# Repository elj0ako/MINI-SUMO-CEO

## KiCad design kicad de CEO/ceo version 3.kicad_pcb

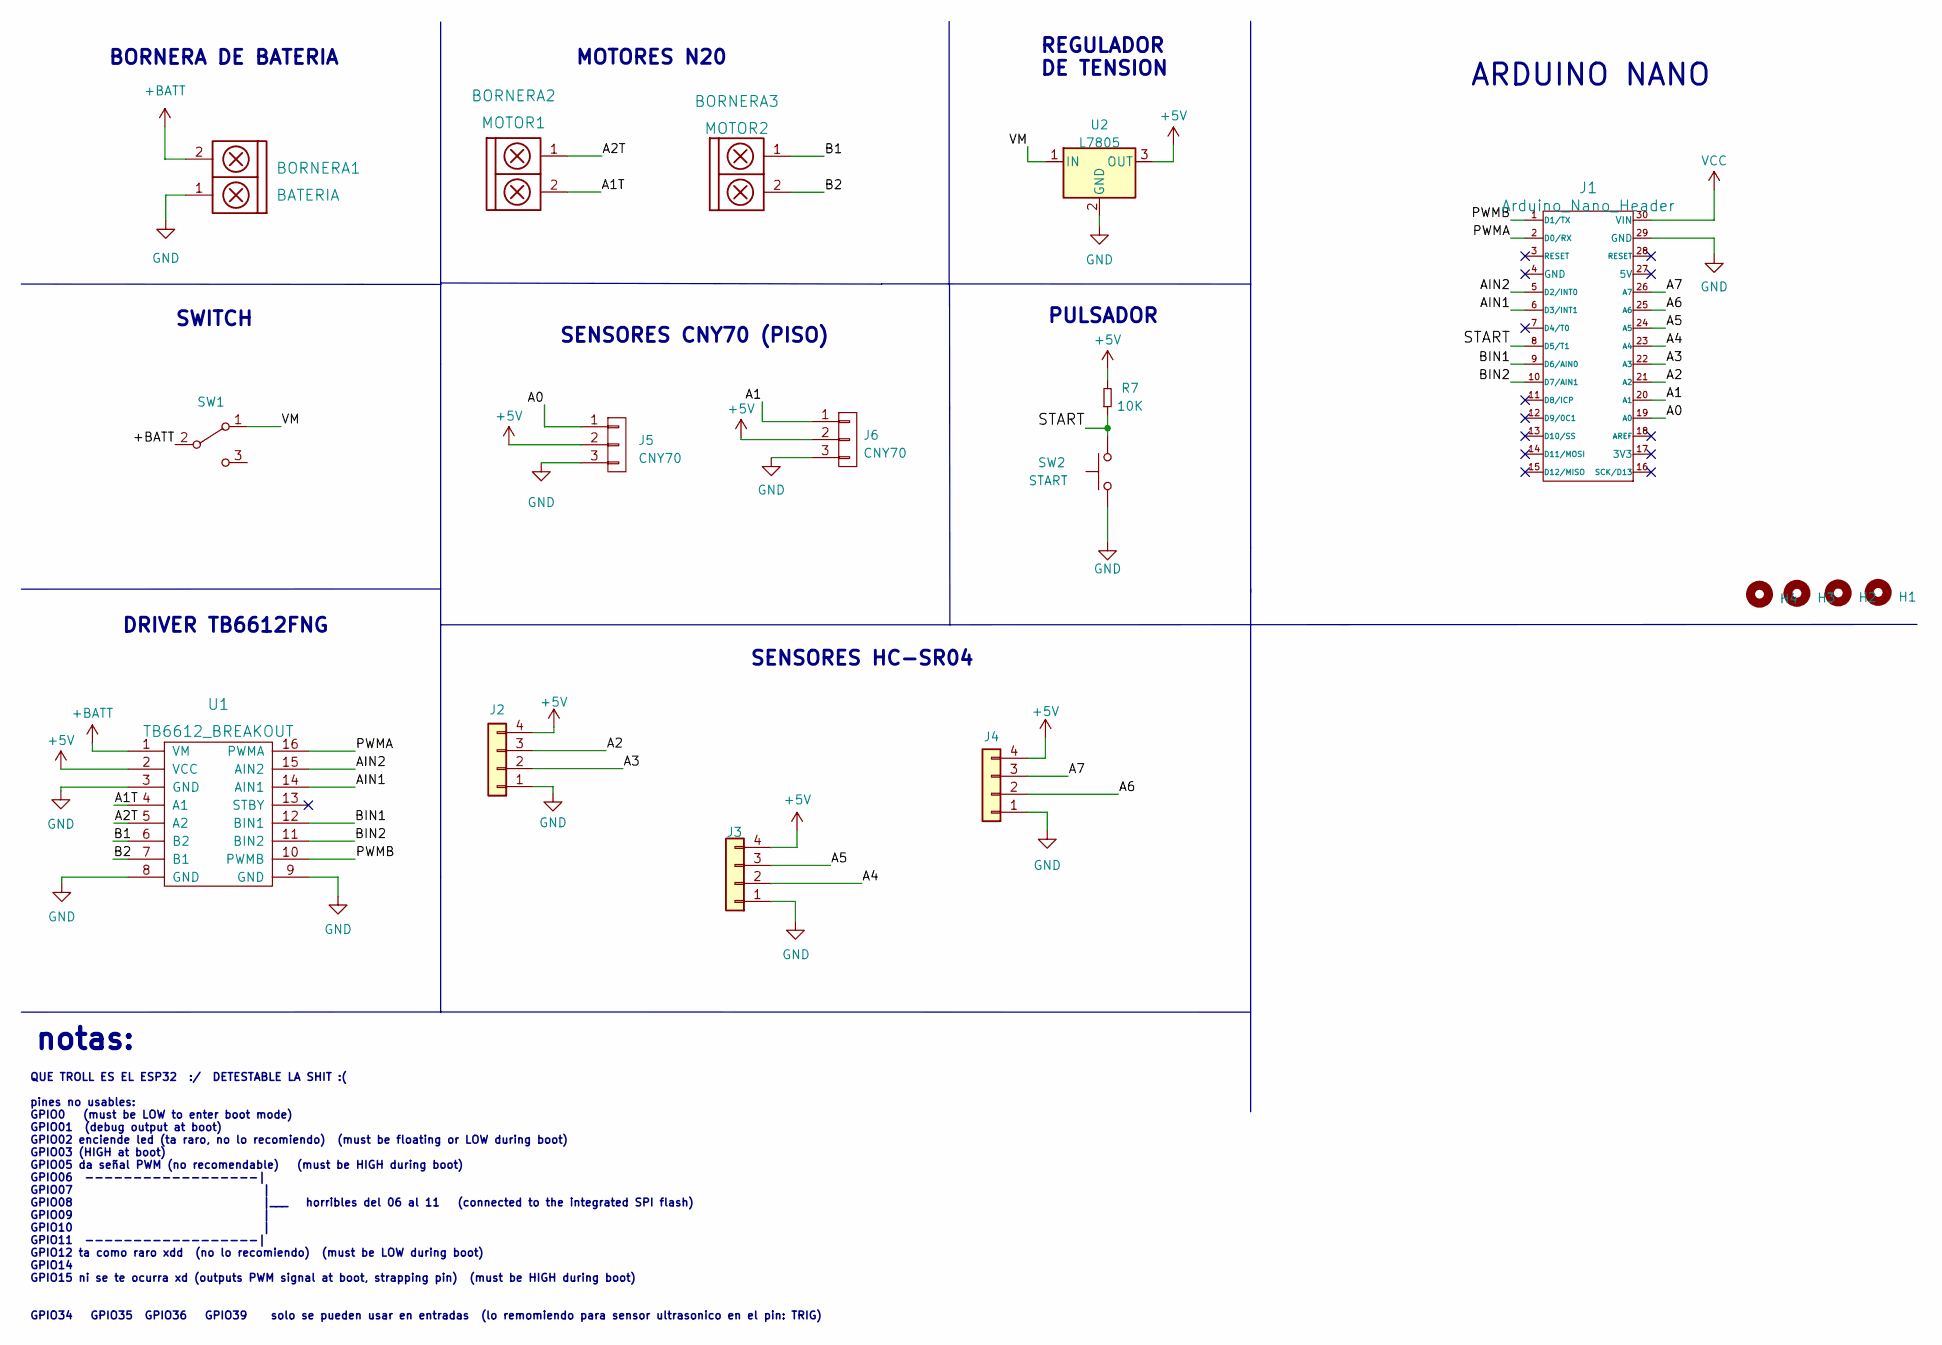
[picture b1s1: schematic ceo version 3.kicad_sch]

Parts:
BORNERA1: BATERIA; BORNERA2
BORNERA2: MOTOR1; BORNERA2
BORNERA3: MOTOR2; BORNERA2
H1, H2, H3, H4: Mounting_Hole; hole_1mm
J1: Arduino_Nano_Header; arduino_nano_header
J2, J3, J4: Conn_01x04; JST_EH_B4B-EH-A_1x04_P2.50mm_Vertical
J5, J6: CNY70; Pin_Header_3
R7: 10K; RES0.3
SW1: SW_SPDT; JST_EH_B2B-EH-A_1x02_P2.50mm_Vertical
SW2: START; JST_EH_B2B-EH-A_1x02_P2.50mm_Vertical
U1: TB6612_BREAKOUT; TB6612_Breakout
U2: L7805; TO-220

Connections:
+5V: J2.4, J3.4, J4.4, J5.2, J6.2, R7.2, U1.2 (VCC), U2.3 (OUT)
+BATT: BORNERA1.2, SW1.2 (B), U1.1 (VM)
/A0: J1.19 (A0), J5.1
/A1: J1.20 (A1), J6.1
/A1T: BORNERA2.2, U1.4 (A1)
/A2: J1.21 (A2), J2.3
/A2T: BORNERA2.1, U1.5 (A2)
/A3: J1.22 (A3), J2.2
/A4: J1.23 (A4), J3.2
/A5: J1.24 (A5), J3.3
/A6: J1.25 (A6), J4.2
/A7: J1.26 (A7), J4.3
/AIN1: J1.6 (D3/INT1), U1.14 (AIN1)
/AIN2: J1.5 (D2/INT0), U1.15 (AIN2)
/B1: BORNERA3.1, U1.6 (B2)
/B2: BORNERA3.2, U1.7 (B1)
/BIN1: J1.9 (D6/AIN0), U1.12 (BIN1)
/BIN2: J1.10 (D7/AIN1), U1.11 (BIN2)
/PWMA: J1.2 (D0/RX), U1.16 (PWMA)
/PWMB: J1.1 (D1/TX), U1.10 (PWMB)
/START: J1.8 (D5/T1), R7.1, SW2.2
/VM: SW1.1 (A), U2.1 (IN)
GND: BORNERA1.1, J1.29 (GND), J2.1, J3.1, J4.1, J5.3, J6.3, SW2.1, U1.3 (GND), U1.8 (GND), U1.9 (GND), U2.2 (GND); also elsewhere on the board
VCC: J1.30 (VIN)

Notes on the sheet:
REGULADOR DE TENSION
BORNERA DE BATERIA
DRIVER TB6612FNG
PULSADOR
QUE TROLL ES EL ESP32 :/ DETESTABLE LA SHIT :( pines no usables: GPIO0 (must be LOW to enter boot mode) GPIO01 (debug output at boot) GPIO02 enciende led (ta raro, no lo recomiendo) (must be floating or LOW during boot) GPIO03 (HIGH at boot) GPIO05 da señal PWM (no recomendable) (must be HIGH durin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
SWITCH
SENSORES HC-SR04
ARDUINO NANO
MOTORES N20
notas:
SENSORES CNY70 (PISO)

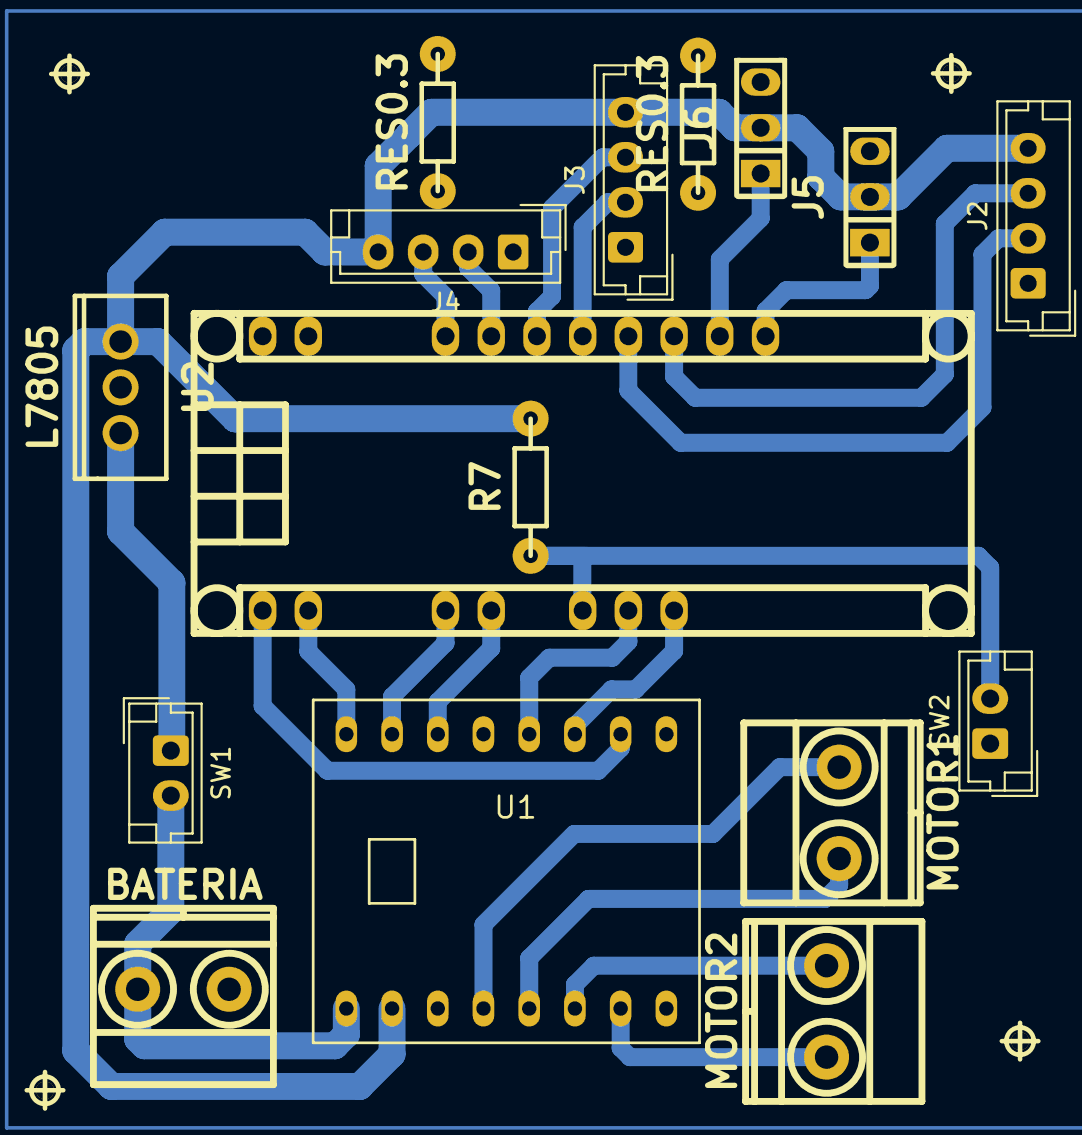
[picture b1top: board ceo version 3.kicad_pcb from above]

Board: 2 copper layers, 20 parts (0 on the bottom side), 23 nets.

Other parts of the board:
RES0.3, RES0.3#2: R*; RES0.3

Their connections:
GND: RES0.3.1, RES0.3.2, RES0.3#2.1, RES0.3#2.2; also elsewhere on the board

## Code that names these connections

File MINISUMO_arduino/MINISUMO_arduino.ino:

int pud = A3; // parlante derecha,trigger rigth
int puc = A4;
//int pui A7;
int mud = A2; // microfono derecha,echo right
int muc = A5; 
//int mui A6; 
//conexiones motor
int pwma = 0;
int ain1 = 3; //derecha
int ain2 = 2;
int pwmb = 1;
int bin1 = 6; //izquierda lado de gnd
int bin2 = 7;
//variables calculo ultrasonico
long dd,dc,di;//distancia derecha,central e izquierda respectivamente
long td,tc,ti;//tiempo derecha,central e izquierda
float vel = 0.017;
//CNY70
int lectura_linea_derecha2 = A0;//IO13
int lectura_linea_izquierda2 = A1;//IO27
int llii;
int lldd;

void setup() {
  Serial.begin(9600);
  delay(5000);
  pinMode(pud, OUTPUT);
  pinMode(puc, OUTPUT);
 // pinMode(pui, OUTPUT);
  pinMode(mud, INPUT);
  pinMode(muc, INPUT);
 // pinMode(mui, INPUT);
  pinMode(ain1, OUTPUT);
  pinMode(ain2, OUTPUT);
  pinMode(bin1, OUTPUT);
  pinMode(bin2, OUTPUT);
  pinMode(lectura_linea_derecha2, INPUT);
  pinMode(lectura_linea_izquierda2, INPUT);
}

void loop() {
      llii = digitalRead(lectura_linea_izquierda2); //Sensor de línea izquierdo
      lldd = digitalRead(lectura_linea_derecha2); //Sensor de línea derecho
      //--------------------------------------------------------------------------------------------------------------------------------------------------
      // estrategia basica
      ultrasonicos();
/*
      while(dc>5 && dd>5){
        // derecha(); delayMicroseconds(30);
      reversa();
      }
      if (dd<=5) 
      {        adelante();      }
      else if (dc<=5)//izquierda 
      {  //      izquierda();        delay(100);        adelante();      
      reversa();
      }
*/
      if(dc<=20)
      { adelante();   }
      else
      { vueltas(); 
      delayMicroseconds(10);}
      CNY70();
    
}
//--------------------------------------------------------------------------------------------------------------------------------------------------
//deteccion ultrasonicos
void ultrasonicos() {
  //deteccion objetivo ultrasonico derecho
  digitalWrite(pud, HIGH);
  delayMicroseconds(10);
  digitalWrite(pud, LOW);
  td = pulseIn(mud, HIGH);
  dd = vel * td;
  Serial.println("distancia derecha=");
  Serial.println(dd);
  
  
  //deteccion objetivo ultrasonico central
  digitalWrite(puc, HIGH);
  delayMicroseconds(10);
  digitalWrite(puc, LOW);
  tc = pulseIn(muc, HIGH);
  dc = vel * tc;
  Serial.println("distancia izquierda=");
  Serial.println(dc)
  ;
//delay();probar cual valor utilizar
}
        //--------------------------------------------------------------------------------------------------------------------------------------------------
     //deteccion de lineas
void CNY70() {
      if (llii == 1) {//1== blanco,por lo que si nuestra superfice de pelea es negra usamos 1
        derecha();
        delayMicroseconds(10);
        adelante();
      }
      if (lldd == 1) {//0=negro,por lo que si actualemente queremos evitar que el robot salga del ring usamos esta configuracion de lldd==1
        izquierda();
        delayMicroseconds(10);
        adelante();
      }
}
//--------------------------------------------------------------------------------------------------------------------------------------------------
//movimientos

void vueltas(){
  derecha(); }

void adelante() {
  digitalWrite(ain1, HIGH);
  digitalWrite(ain2, LOW);
  digitalWrite(bin1, HIGH);
  digitalWrite(bin2, LOW);
}
//sobre su propio eje
void derecha() {
  digitalWrite(ain1, LOW);
  digitalWrite(ain2, HIGH);
  digitalWrite(bin1, HIGH);
  digitalWrite(bin2, LOW);
}
//sobre su propio eje
void izquierda() {
  digitalWrite(ain1, HIGH);
  digitalWrite(ain2, LOW);
  digitalWrite(bin1, LOW);
  digitalWrite(bin2, HIGH);
}
//marcha atras
void reversa() {
  digitalWrite(ain1, LOW);
  digitalWrite(ain2, HIGH);
  digitalWrite(bin1, LOW);
  digitalWrite(bin2, HIGH);
}

void detener() {
  digitalWrite(ain1, LOW);
  digitalWrite(ain2, LOW);
  digitalWrite(bin1, LOW);
  digitalWrite(bin2, LOW);
}

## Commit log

2023-12-05 se agrega el proyecto
